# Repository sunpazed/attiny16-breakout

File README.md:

## Breakout board for the attiny1616 (20 VQFN)

To keep things small (DIP-16), only a subset of pins are avalable — Port A pins (PA0-PA6) and Port B pins (PB0-PB5), along with a single PC0 pin;

<center></center>

A small 0.1uF decoupling capacitor is also included to simplify usage on the breadboard.

<center></center>

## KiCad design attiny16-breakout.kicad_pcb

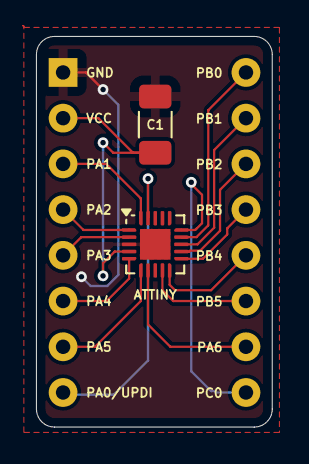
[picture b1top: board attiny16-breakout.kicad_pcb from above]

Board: 2 copper layers, 13.1 x 21.7 mm, 3 parts (0 on the bottom side), 16 nets.

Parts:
ATTINY: ATtiny1616-M; VQFN-20-1EP_3x3mm_P0.4mm_EP1.7x1.7mm
C1: C; C_1206_3216Metric_Pad1.33x1.80mm_HandSolder
J1: Conn_02x08_Counter_Clockwise; DIP-16_W10.16mm

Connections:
GND: ATTINY.3 (GND), ATTINY.21 (GND), C1.2, J1.1
unnamed: ATTINY.20 (PA1), J1.3
unnamed: ATTINY.1 (PA2), J1.4
unnamed: ATTINY.2 (PA3), J1.5
unnamed: ATTINY.5 (PA4), J1.6
unnamed: ATTINY.6 (PA5), J1.7
unnamed: ATTINY.19 (~RESET/PA0), J1.8
unnamed: ATTINY.15 (PC0), J1.9
unnamed: ATTINY.7 (PA6), J1.10
unnamed: ATTINY.9 (PB5), J1.11
unnamed: ATTINY.10 (PB4), J1.12
unnamed: ATTINY.11 (PB3), J1.13
unnamed: ATTINY.12 (PB2), J1.14
unnamed: ATTINY.13 (PB1), J1.15
unnamed: ATTINY.14 (PB0), J1.16
VCC: ATTINY.4 (VCC), C1.1, J1.2

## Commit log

2024-10-07 updated readme and lic
